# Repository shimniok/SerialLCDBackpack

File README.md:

# SerialLCDBackpack
Serial interface backpack for HD44780 LCD character displays

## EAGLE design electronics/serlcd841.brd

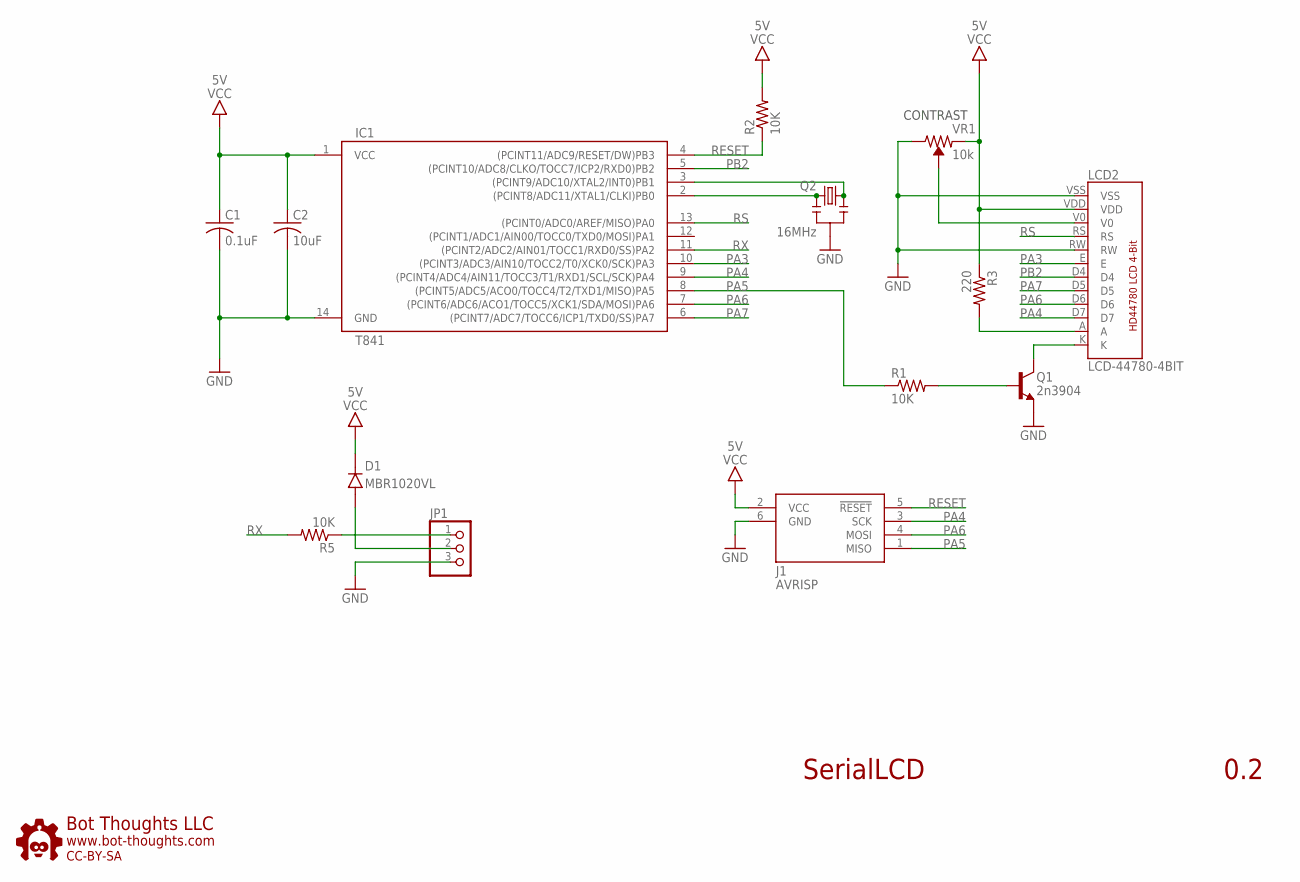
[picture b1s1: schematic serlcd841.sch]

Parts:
C1: 0.1uF; 0603
C2: 10uF; 1206
D1: MBR1020VL; SOD123FL
IC1: T841; SOIC14N
J1: AVRISP; CON6P2R
JP1: PINHD-1X03_2.54-S; 1X03-S
LCD2: LCD-44780-4BIT; LCD16SIP
Q1: 2n3904; SOT-23
Q2: 16MHz; CSTCE_V_C
R1, R2, R5: 10K; 0603
R3: 220; 0603
U$6: BTLOGO-LOGO-MD; BTLOGOM
VR1: 10k; TRIMPOT-SMD-TC33X

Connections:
A: LCD2.A, R3.2
GND: C1.2 (-), C2.2 (-), IC1.14 (GND), J1.6 (GND), JP1.3, LCD2.RW, LCD2.VSS, Q1.2 (E), Q2.GND, VR1.1 (CW)
unnamed: D1.A, JP1.2
unnamed: IC1.2 ((PCINT8/ADC11/XTAL1/CLKI)PB0), Q2.X2
unnamed: IC1.3 ((PCINT9/ADC10/XTAL2/INT0)PB1), Q2.X1
unnamed: Q1.3 (B), R1.2
unnamed: LCD2.K, Q1.1 (C)
PA3: IC1.10 ((PCINT3/ADC3/AIN10/TOCC2/T0/XCK0/SCK)PA3), LCD2.E
PA4: IC1.9 ((PCINT4/ADC4/AIN11/TOCC3/T1/RXD1/SCL/SC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), J1.3 (SCK), LCD2.D7
PA5: IC1.8 ((PCINT5/ADC5/ACO0/TOCC4/T2/TXD1/MISO)PA5), J1.1 (MISO), R1.1
PA6: IC1.7 ((PCINT6/ADC6/ACO1/TOCC5/XCK1/SDA/MOSI)P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), J1.4 (MOSI), LCD2.D6
PA7: IC1.6 ((PCINT7/ADC7/TOCC6/ICP1/TXD0/SS)PA7), LCD2.D5
PB2: IC1.5 ((PCINT10/ADC8/CLKO/TOCC7/ICP2/RXD0)PB2), LCD2.D4
RESET: IC1.4 ((PCINT11/ADC9/RESET/DW)PB3), J1.5 (!RESET), R2.1
RS: IC1.13 ((PCINT0/ADC0/AREF/MISO)PA0), LCD2.RS
RX: IC1.11 ((PCINT2/ADC2/AIN01/TOCC1/RXD0/SS)PA2), R5.2
RXI: JP1.1, R5.1
VCC: C1.1 (+), C2.1 (+), D1.C, IC1.1 (VCC), J1.2 (VCC), LCD2.VDD, R2.2, R3.1, VR1.3 (CCW)
VO: LCD2.V0, VR1.2 (WIPER)

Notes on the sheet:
SerialLCD
0.2
CONTRAST

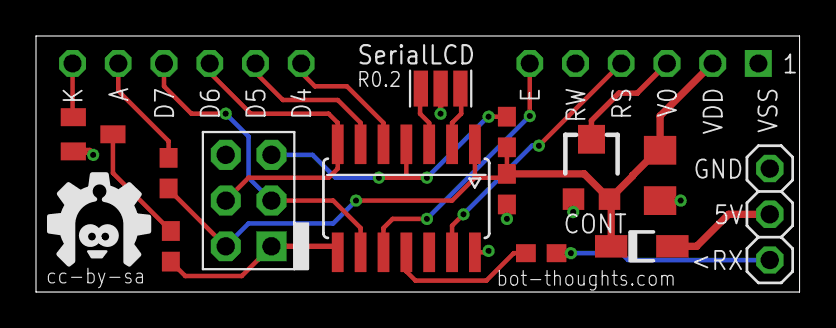
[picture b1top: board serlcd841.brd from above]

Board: 2 copper layers, 42.4 x 14.2 mm, 15 parts (0 on the bottom side), 19 nets.

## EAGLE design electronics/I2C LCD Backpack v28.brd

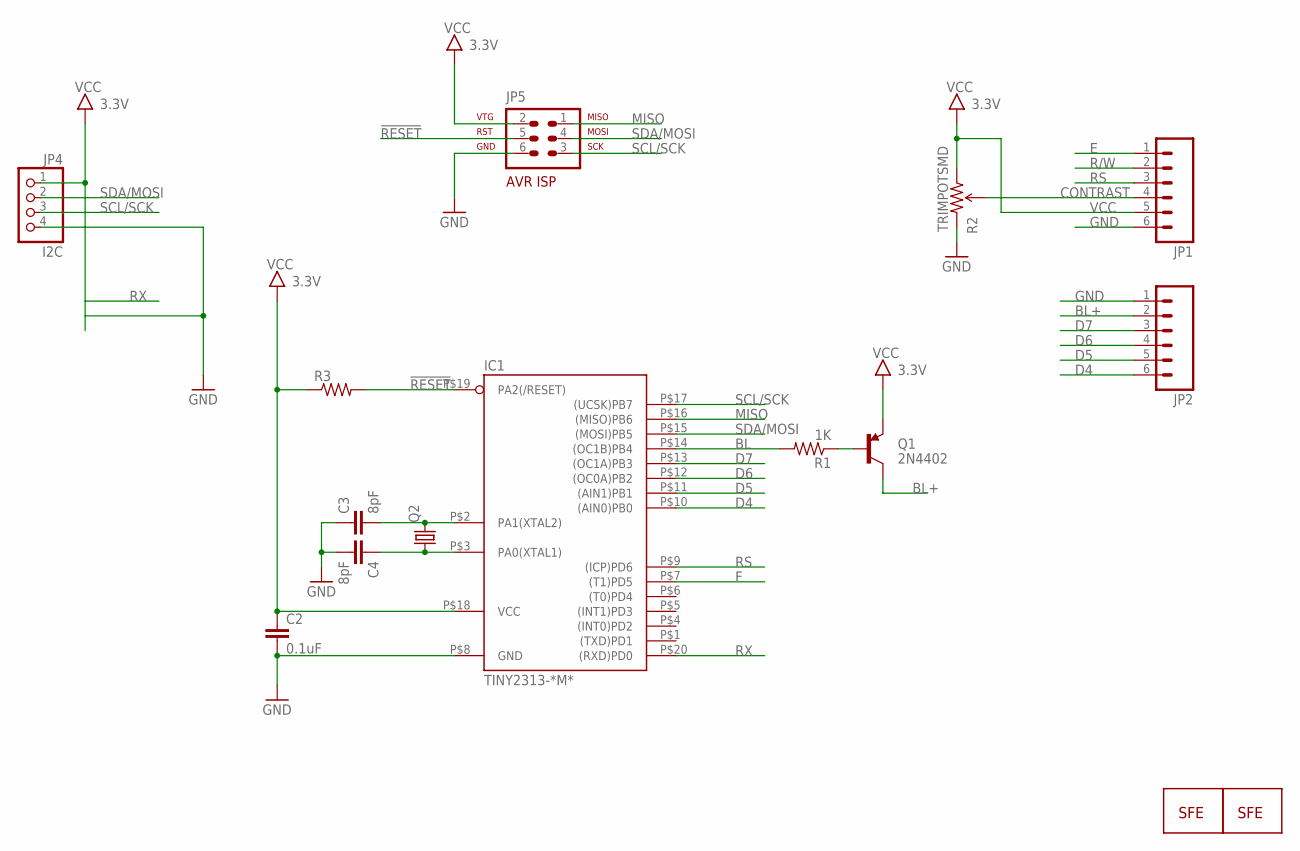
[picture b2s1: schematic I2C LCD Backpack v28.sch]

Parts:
C2: 0.1uF; 0603-CAP
C3, C4: 8pF; 0603-CAP
IC1: TINY2313-*M*; MLF20
JP1, JP2: M06LOCK; 1X06_LOCK
JP4: I2C; 1X04-S
JP5: AVR-ISP-6
Q1: 2N4402; SOT23-3
Q2: CRYSTALNDK5X3; NDK_2PAD_5X3
R1: 1K; 0402-RES
R2: TRIMPOTSMD; TRIMPOT-3MM
R3: R-US_R0603; R0603
U$2: LOGO-FLAME-LARGE
U$5: LOGO-SFENEW; SFE-NEW-WEBLOGO

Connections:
!RESET: IC1.P$19 (PA2(/RESET)), JP5.5, R3.2
BL: IC1.P$14 ((OC1B)PB4), R1.2
BL+: JP2.2, Q1.3 (C)
CONTRAST: JP1.4, R2.2 (WIPER)
D4: IC1.P$10 ((AIN0)PB0), JP2.6
D5: IC1.P$11 ((AIN1)PB1), JP2.5
D6: IC1.P$12 ((OC0A)PB2), JP2.4
D7: IC1.P$13 ((OC1A)PB3), JP2.3
E: JP1.1
F: IC1.P$7 ((T1)PD5)
GND: C2.2, C3.1, C4.2, IC1.P$8 (GND), JP1.6, JP2.1, JP4.4, JP5.6, R2.3 (CW)
MISO: IC1.P$16 ((MISO)PB6), JP5.1
unnamed: C4.1, IC1.P$3 (PA0(XTAL1)), Q2.P$1 (1)
unnamed: C3.2, IC1.P$2 (PA1(XTAL2)), Q2.P$2 (2)
unnamed: Q1.1 (B), R1.1
R/W: JP1.2
RS: IC1.P$9 ((ICP)PD6), JP1.3
RX: IC1.P$20 ((RXD)PD0)
SCL/SCK: IC1.P$17 ((UCSK)PB7), JP4.3, JP5.3
SDA/MOSI: IC1.P$15 ((MOSI)PB5), JP4.2, JP5.4
VCC: C2.1, IC1.P$18 (VCC), JP1.5, JP4.1, JP5.2, Q1.2 (E), R2.1 (CCW), R3.1

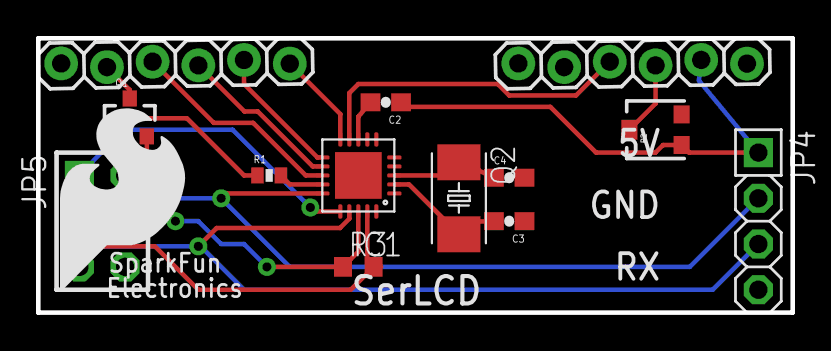
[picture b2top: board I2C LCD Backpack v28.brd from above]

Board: 2 copper layers, 41.9 x 15.2 mm, 15 parts (1 on the bottom side), 17 nets.

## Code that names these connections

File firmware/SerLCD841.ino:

/* Serial LCD ATTiny841
 * by Michael Shimniok (www.bot-thoughts.com)
 */

#include <LiquidCrystal.h>

#define RS    10 // PA0
#define EN     7 // PA3
#define DATA4  2 // PB2
#define DATA5  3 // PA7
#define DATA6  4 // PA6
#define DATA7  6 // PA4

#define LIGHT  5 // PA5

// initialize the library with the numbers of the interface pins
LiquidCrystal lcd(RS, EN, DATA4, DATA5, DATA6, DATA7);

void setup() {
  lcd_init();
  Serial.begin(9600);
}

void loop() {
  char buf[16];
  // set the cursor to column 0, line 1
  // (note: line 1 is the second row, since counting begins with 0):
  while (Serial.available()) {
    process(Serial.read() & 0xff);
  }
}

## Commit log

2017-05-22 initial version
2017-05-22 updated footprint for lcd, layout tweaks, switched some pins.
2017-05-22 backlight nmos rotation
2017-05-22 implemented backlight commands
2017-06-09 Corrected ISP connections, removed transistor for
2017-06-09 added arduino based firmware
2017-06-09 removed weird link
2017-06-09 created arduino sketch dir
2017-06-09 fixed wire/pad clearance issues
2017-06-09 updated gerbers, zip
2017-06-27 added readme
2017-06-27 added code to set high current mode on PA5 for led backlight
2017-06-27 added commented-out code for EEPROM screen size & brightness
2021-02-10 i don't remember :(

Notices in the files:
electronics/serlcd841.brd:
cc-by-sa
parts and their libraries:
SparkFun-Resistors: Licensing: Creative Commons ShareAlike 4.0 International - https://creativecommons.org/licenses/by-sa/4.0
